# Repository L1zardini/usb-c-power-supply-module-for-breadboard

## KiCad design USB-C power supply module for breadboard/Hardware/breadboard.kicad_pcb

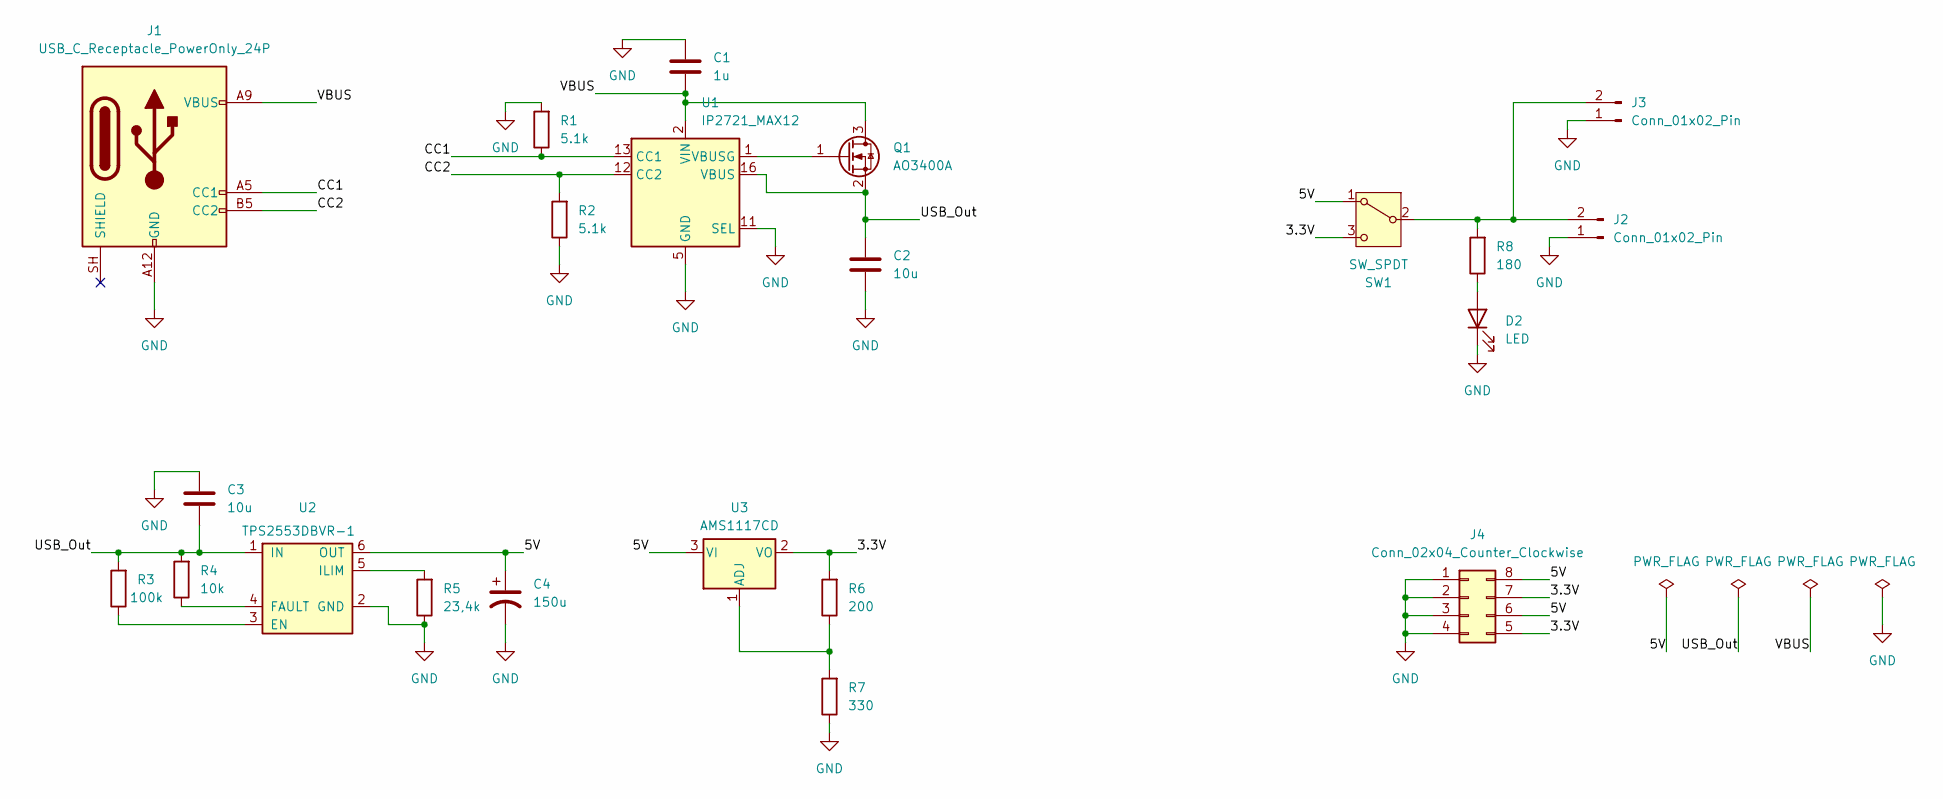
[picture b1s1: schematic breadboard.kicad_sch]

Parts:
C1: 1u; C_0402_1005Metric
C2: 10u; C_1206_3216Metric
C3: 10u; C_0603_1608Metric
C4: 150u; CP_Elec_4x5.4
D2: LED; LED_D3.0mm
J1: USB_C_Receptacle_PowerOnly_24P; USB_C_Receptacle_Amphenol_12401610E4-2A
J2, J3: Conn_01x02_Pin; PinHeader_1x02_P1.00mm_Vertical
J4: Conn_02x04_Counter_Clockwise; PinHeader_2x04_P1.00mm_Vertical
Q1: AO3400A; SOT-23
R1, R2: 5.1k; R_0603_1608Metric
R3: 100k; R_0603_1608Metric
R4: 10k; R_0603_1608Metric
R5: 23,4k; R_0603_1608Metric
R6: 200; R_0603_1608Metric
R7: 330; R_0603_1608Metric
R8: 180; R_0603_1608Metric
SW1: SW_SPDT; SW_Slide-03_Wuerth-WS-SLTV_10x2.5x6.4_P2.54mm
U1: IP2721_MAX12; TSSOP-16_4.4x5mm_P0.65mm
U2: TPS2553DBVR-1; SOT-23-6
U3: AMS1117CD; TO-252-3_TabPin2

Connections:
/3.3V: J4.5, J4.7, R6.2, SW1.3 (C), U3.2 (VO)
/5V: C4.1, J4.6, J4.8, SW1.1 (A), U2.6 (OUT), U3.3 (VI)
/CC1: J1.A5 (CC1), R1.1, U1.13 (CC1)
/CC2: J1.B5 (CC2), R2.2, U1.12 (CC2)
/USB_Out: C2.1, C3.2, Q1.2 (S), R3.2, R4.2, U1.16 (VBUS), U2.1 (IN)
/VBUS: C1.2, J1.A4 (VBUS), J1.A9 (VBUS), J1.B4 (VBUS), J1.B9 (VBUS), Q1.3 (D), U1.2 (VIN)
GND: C1.1, C2.2, C3.1, C4.2, D2.1 (K), J1.A1 (GND), J1.A12 (GND), J1.B1 (GND), J1.B12 (GND), J2.1, J3.1, J4.1, J4.2, J4.3, J4.4, R1.2, R2.1, R5.1, R7.1, U1.5 (GND), U1.11 (SEL), U2.2 (GND)
unnamed: D2.2 (A), R8.1
unnamed: J2.2, J3.2, R8.2, SW1.2 (B)
unnamed: Q1.1 (G), U1.1 (VBUSG)
unnamed: R3.1, U2.3 (EN)
unnamed: R4.1, U2.4 (FAULT)
unnamed: R5.2, U2.5 (ILIM)
unnamed: R6.1, R7.2, U3.1 (ADJ)

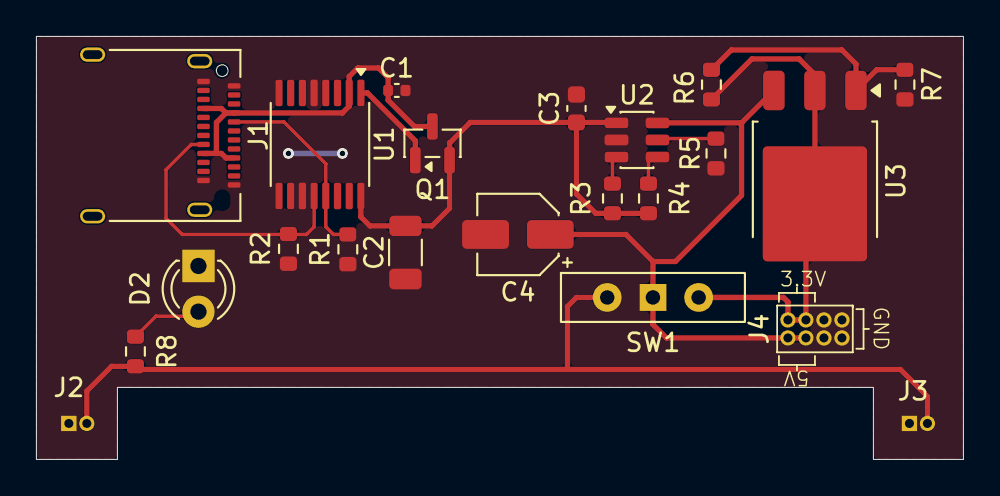
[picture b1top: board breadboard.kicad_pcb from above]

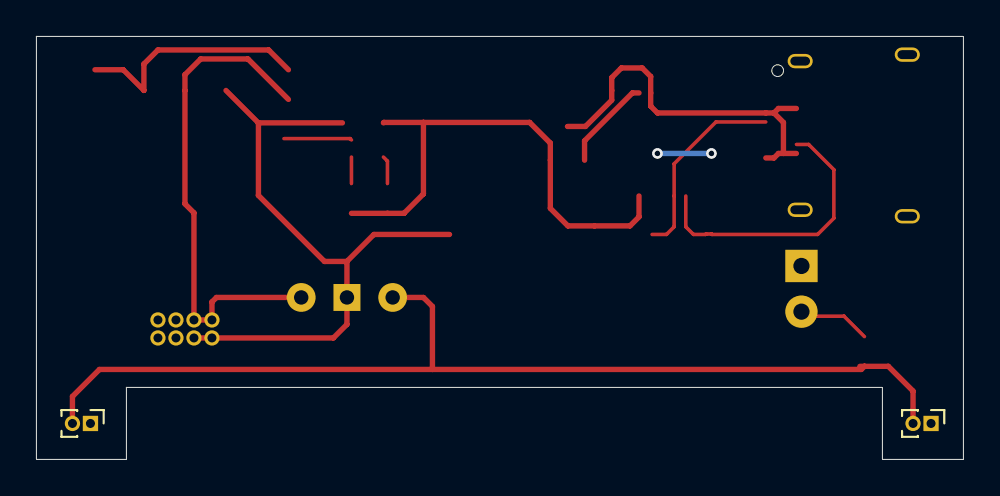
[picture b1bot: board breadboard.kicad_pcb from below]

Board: 2 copper layers, 51.5 x 23.5 mm, 22 parts (2 on the bottom side), 14 nets.

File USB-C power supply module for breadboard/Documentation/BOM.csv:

"Reference","Value","Footprint","Qty"
"C1","1u","Capacitor_SMD:C_0402_1005Metric","1"
"C2","10u","Capacitor_SMD:C_1206_3216Metric","1"
"C3","10u","Capacitor_SMD:C_0603_1608Metric","1"
"C4","150u","Capacitor_SMD:CP_Elec_4x5.4","1"
"D2","LED","LED_THT:LED_D3.0mm","1"
"J1","USB_C_Receptacle_PowerOnly_24P","Connector_USB:USB_C_Receptacle_Amphenol_12401610E4-2A","1"
"J2","Conn_01x02_Pin","Connector_PinHeader_1.00mm:PinHeader_1x02_P1.00mm_Vertical","1"
"J3","Conn_01x02_Pin","Connector_PinHeader_1.00mm:PinHeader_1x02_P1.00mm_Vertical","1"
"J4","Conn_02x04_Counter_Clockwise","Symbol:PinHeader_2x04_P1.00mm_Vertical","1"
"Q1","AO3400A","Package_TO_SOT_SMD:SOT-23","1"
"R1","5.1k","Resistor_SMD:R_0603_1608Metric","1"
"R2","5.1k","Resistor_SMD:R_0603_1608Metric","1"
"R3","100k","Resistor_SMD:R_0603_1608Metric","1"
"R4","10k","Resistor_SMD:R_0603_1608Metric","1"
"R5","23,4k","Resistor_SMD:R_0603_1608Metric","1"
"R6","200","Resistor_SMD:R_0603_1608Metric","1"
"R7","330","Resistor_SMD:R_0603_1608Metric","1"
"R8","180","Resistor_SMD:R_0603_1608Metric","1"
"SW1","SW_SPDT","Button_Switch_THT:SW_Slide-03_Wuerth-WS-SLTV_10x2.5x6.4_P2.54mm","1"
"U1","IP2721_MAX12","Package_SO:TSSOP-16_4.4x5mm_P0.65mm","1"
"U2","TPS2553DBVR-1","Package_TO_SOT_SMD:SOT-23-6","1"
"U3","AMS1117CD","Package_TO_SOT_SMD:TO-252-3_TabPin2","1"
